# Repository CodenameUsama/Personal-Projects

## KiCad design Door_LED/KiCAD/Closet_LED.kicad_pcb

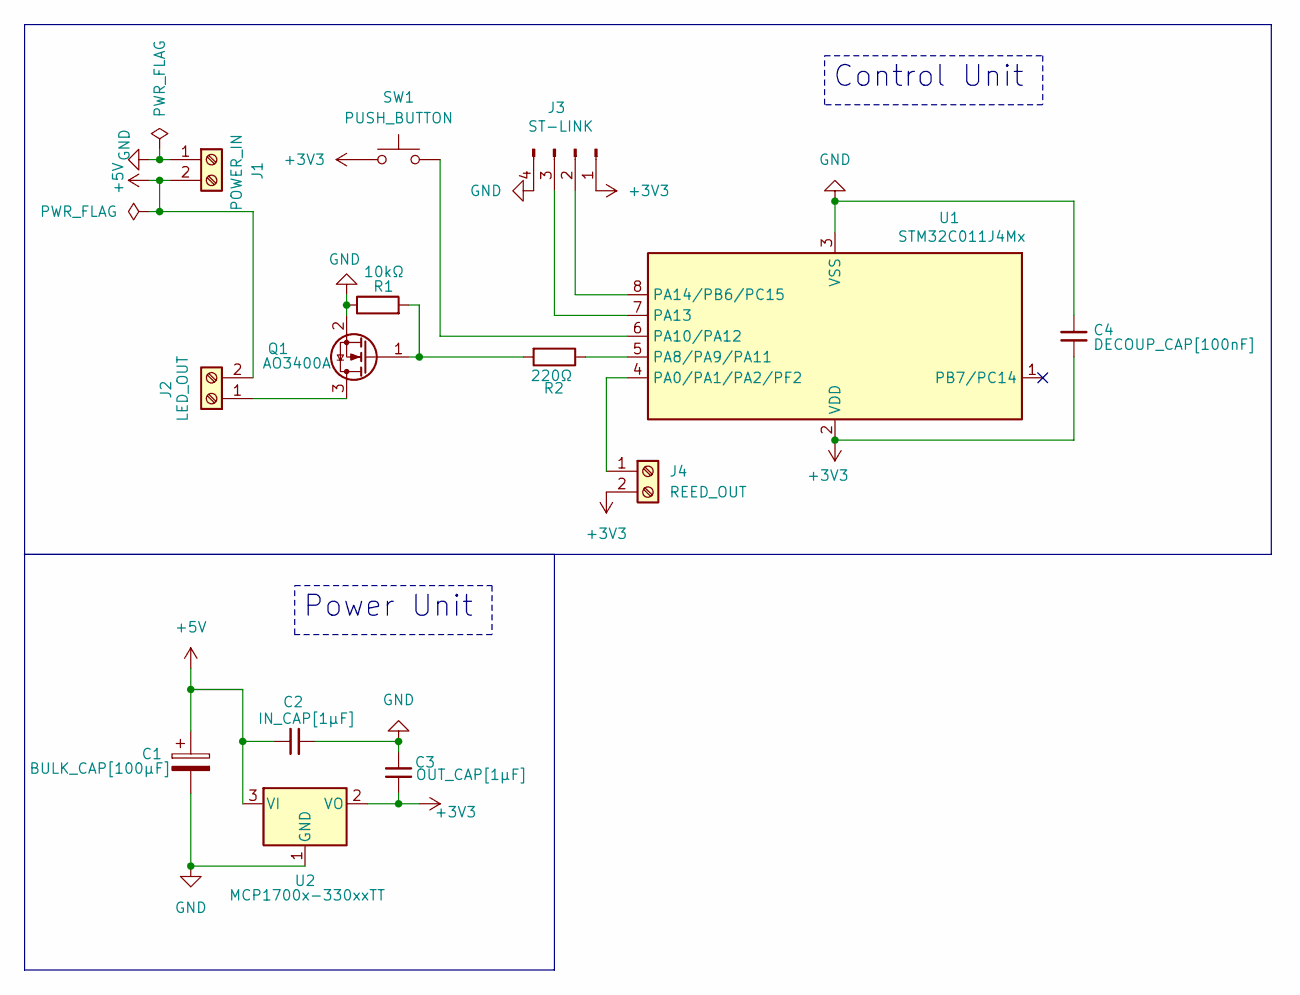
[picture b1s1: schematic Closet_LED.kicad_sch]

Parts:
C1: BULK_CAP[100µF]; CP_Radial_D8.0mm_P3.50mm
C2: IN_CAP[1µF]; C_0805_2012Metric_Pad1.18x1.45mm_HandSolder
C3: OUT_CAP[1µF]; C_0805_2012Metric_Pad1.18x1.45mm_HandSolder
C4: DECOUP_CAP[100nF]; C_0805_2012Metric_Pad1.18x1.45mm_HandSolder
J1: POWER_IN; TerminalBlock_MaiXu_MX126-5.0-02P_1x02_P5.00mm
J2: LED_OUT; TerminalBlock_MaiXu_MX126-5.0-02P_1x02_P5.00mm
J3: ST-LINK; PinHeader_1x04_P2.54mm_Horizontal
J4: REED_OUT; TerminalBlock_MaiXu_MX126-5.0-02P_1x02_P5.00mm
Q1: AO3400A; SOT-23-3
R1: 10kΩ; R_0805_2012Metric
R2: 220Ω; R_0805_2012Metric
SW1: PUSH_BUTTON; SW_PUSH_6mm
U1: STM32C011J4Mx; SOIC-8_3.9x4.9mm_P1.27mm
U2: MCP1700x-330xxTT; SOT-23

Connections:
+3V3: C3.1, C4.2, J3.1, J4.2, SW1.1, U1.2 (VDD), U2.2 (VO)
+5V: C1.1, C2.2, J1.2, J2.2, U2.3 (VI)
GND: C1.2, C2.1, C3.2, C4.1, J1.1, J3.4, Q1.2 (S), R1.1, U1.3 (VSS), U2.1 (GND)
unnamed: J2.1, Q1.3 (D)
unnamed: J3.2, U1.8 (PA14/PB6/PC15)
unnamed: J3.3, U1.7 (PA13)
unnamed: J4.1, U1.4 (PA0/PA1/PA2/PF2)
unnamed: Q1.1 (G), R1.2, R2.2
unnamed: R2.1, U1.5 (PA8/PA9/PA11)
unnamed: SW1.2, U1.6 (PA10/PA12)

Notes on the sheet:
Power Unit
Control Unit

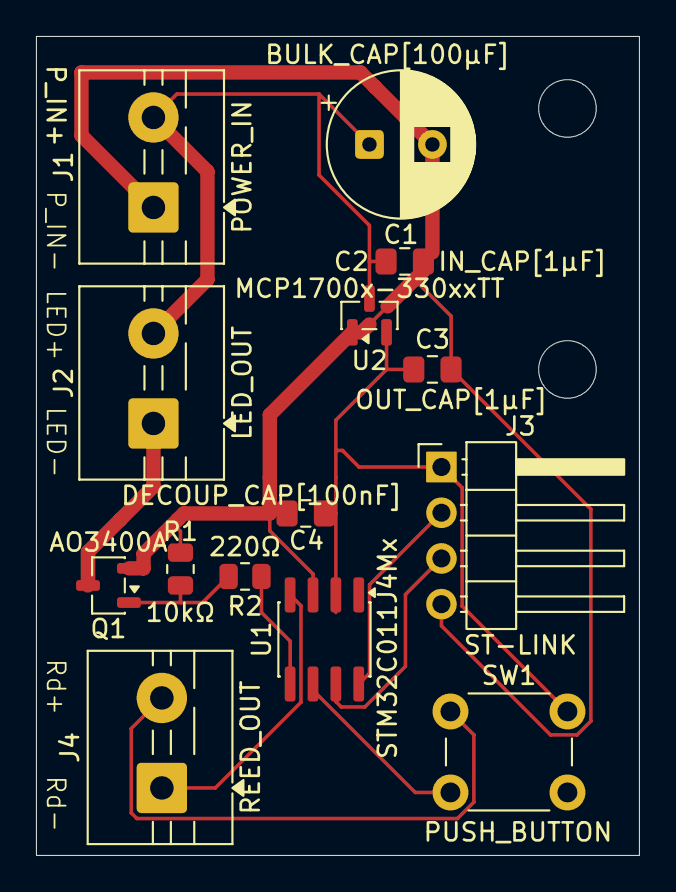
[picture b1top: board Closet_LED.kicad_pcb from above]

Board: 2 copper layers, 33.5 x 45.5 mm, 14 parts (0 on the bottom side), 10 nets.
